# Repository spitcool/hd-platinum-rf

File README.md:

<!-- SPDX-FileCopyrightText: 2026 Christopher Spitler -->
<!-- SPDX-License-Identifier: CC-BY-SA-4.0 OR AGPL-3.0-or-later -->

# hd-platinum-rf

An open-source replacement bridge for Hunter Douglas Platinum blinds and shades,
built around ESP32, with protocol documentation and tools for ongoing research.

## The problem

Hunter Douglas Platinum shades rely on discontinued bridges and remotes. When
that control hardware fails, otherwise working shades become harder to use and
integrate with home automation. The legacy LAN and RF protocols need to be
understood and documented so that replacement controllers can keep them useful.

## The solution

We're building an ESP32-S3 gateway that provides local shade control through a
touchscreen, web interface, and the legacy Platinum network protocol. The current
hardware design uses an M5Stack CoreS3 SE, an Ethernet base, and a custom radio
carrier. Python research tools and a bridge emulator help us capture, understand,
and validate the protocols as the device takes shape.

This project targets the **Platinum generation** of products. It is independent
and unofficial, and does not target the later PowerView system.

## Project status

**We're currently confirming the RF protocols and designing the hardware
implementation.** The project is experimental; the ESP32 gateway is not yet a
validated replacement for the original bridge.

- [x] Document observed LAN commands and initial RF packet formats.
- [x] Build research tools and a bridge emulator with limited observed shade-control results.
- [x] Implement an ESP32-S3 firmware prototype with local controls.
- [ ] Confirm all RF protocols, command timing, and product-specific behavior.
- [ ] Complete and qualify the ESP32 hardware design.
- [ ] Validate enrollment, repeatability, and broader shade compatibility.
- [ ] Validate integrations such as Control4.

See the [RF validation plan](docs/rf-validation-plan.md) for the evidence and
remaining work. Successful software builds and simulations do not establish
physical RF compatibility.

## Getting started

- **Build your own device:** [ESP32 build, flashing, and device BOM](docs/esp32-build.md).
- **Explore the implementation:** [Project details and research tools](docs/project-details.md), including CLI setup and bridge emulator commands.
- **Understand the protocols:** [LAN protocol](docs/lan-protocol.md) and [RF protocol](docs/rf-protocol.md).
- **Review the hardware:** [Carrier design and assembly](hardware/README.md).
- **Run tests or help with RF validation:** [Testing guide](docs/testing.md) and [bench equipment BOM](docs/bom.md).

## Contributing

Protocol validation, hardware review, firmware testing, and documentation
contributions are welcome. Read [CONTRIBUTING.md](CONTRIBUTING.md) for the
workflow, test requirements, and DCO sign-off. Remove private installation data
from shared captures and reports. Use the
[issue tracker](https://github.com/spitcool/hd-platinum-rf/issues) for bugs and
feature discussions.

## License

Host software is [AGPL-3.0-or-later](LICENSE); project firmware is
[GPL-2.0-or-later](LICENSES/GPL-2.0-or-later.txt). Documentation is available under
[CC BY-SA 4.0](LICENSES/CC-BY-SA-4.0.txt) or AGPL-3.0-or-later. See
[LICENSING.md](LICENSING.md) for component boundaries and
[CREDITS.md](CREDITS.md) for third-party attribution.

Hunter Douglas and its product names are trademarks of their respective owner.

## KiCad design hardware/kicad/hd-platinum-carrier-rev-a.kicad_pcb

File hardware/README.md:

<!--
SPDX-FileCopyrightText: 2026 Christopher Spitler
SPDX-License-Identifier: CC-BY-SA-4.0 OR AGPL-3.0-or-later
-->

# Platinum M5Stack radio carrier

This hardware adds an enclosed 2.4 GHz radio to an M5Stack CoreS3 SE and Base
LAN v1.2 stack. The intended product is an Ethernet-connected Platinum shade
bridge with a local TCP service and a small web interface. The radio PCB is designed for
a Module13.2 frame; a coax cable connects it to an external antenna.

**Revision A is an engineering first article.** The CAD and manufacturing
outputs describe a board to build and qualify. They do not establish measured
enclosure fit, RF performance, or compatibility with every Platinum shade.
Complete the [acceptance procedure](manufacturing/acceptance-test.md) before
releasing a repeat build for other users.

The recorded KiCad checks pass with **zero ERC errors/warnings, zero PCB DRC
violations, zero unconnected items and zero schematic-parity differences**;
there are no DRC exclusions. Independent checks passed 95 mechanical/orientation
assertions and 41 manufacturing-package checks and matched 65 connected schematic pins on 17 intended nets.
These check the design files. Physical fit, RF measurements, native-radio
interoperability and the ESP32 firmware remain qualification work. See the
[design-package review](design/final-review.md) for the evidence and limits.

## Appliance architecture

The [final assembly drawing](manufacturing/final-assembly.pdf) shows the
exploded stack, assembled enclosure and a cutaway of the M032 radio layer.
See the [illustrated assembly guide](manufacturing/final-assembly.md) for the
part list and sequence, or open the [SVG](manufacturing/final-assembly.svg).

```text
M5Stack CoreS3 SE K128-SE
  ESP32-S3: application, touchscreen, TCP and HTTP services
                  │ M-Bus power and GPIO
M032 Module13.2 frame + this replacement carrier PCB
  5 V → separate 3.3 V regulator → NiceRF RF2401F20
  dedicated SPI and control GPIO → 2.4 GHz radio
  RF connector → internal coax → external antenna
                  │ all 30 M-Bus contacts pass through
M5Stack Base LAN v1.2 K012-B-V12
  W5500 wired Ethernet and appliance base
```

The custom PCB replaces the M032 prototyping PCB. It is not an adapter soldered
onto the M032 hole grid. The Base LAN and CoreS3 SE remain purchased products.
This carrier does not add Ethernet, PoE, a charger, or another processor.

The radio has a separate SPI bus from the W5500. It uses GPIO 6/5/8 for
SCK/MOSI/MISO and GPIO 18/17/10 for CSN/CE/IRQ. The carrier derives its radio
supply from M-Bus 5 V; its RF 3.3 V rail must not connect to the M5Stack's 3.3 V
rail. The [electrical evidence](design/electrical-evidence.md) and
[pin assignment](design/pin-assignment.csv) record the interface details.

## Files and reproducible build

The complete [hardware review archive](hd-platinum-carrier-rev-a-review.zip)
contains the native source, manufacturing outputs, evidence, tools and license
notices. The archive is for engineering review and first-article planning.
The [tool instructions](tools/README.md) explain how to validate the native CAD
or regenerate it from source. A complete source regeneration and export passed
on the recorded KiCad 9.0.8 toolchain.

## What to send to a manufacturer

Open [the editable KiCad PCB](kicad/hd-platinum-carrier-rev-a.kicad_pcb) and
[schematic](kicad/hd-platinum-carrier-rev-a.kicad_sch), or review the exported
[schematic PDF](manufacturing/schematic.pdf) and
[bottom assembly drawing](manufacturing/assembly-bottom.pdf). The PCB is
50 × 50 mm with all surface-mount parts on the inward-facing bottom side.

Send the [Gerber/drill ZIP](manufacturing/hd-platinum-carrier-rev-a-gerbers.zip),
[PCBA BOM](manufacturing/bom.csv), [placement file](manufacturing/positions.csv),
the [fabrication drawing](manufacturing/fabrication-drawing.pdf),
assembly drawings and these documents together. The [board-only STEP](manufacturing/carrier-board-only.step)
and [outline DXF](manufacturing/board-outline.dxf) support enclosure review;
the STEP does not include components or an enclosure. Keep every file in a handoff
at the same board revision. The editable project and generation tools remain
the source for future revisions.

| Document | Purpose |
| --- | --- |
| [Final assembly drawing and guide](manufacturing/final-assembly.md) | M5Stack stack order, carrier location inside M032, antenna and cable arrangement |
| [Fabrication specification](manufacturing/fabrication.md) | Board construction, RF geometry, drill and DFM requirements |
| [Assembly instructions](manufacturing/assembly.md) | Component handling, orientation, stack assembly and coax installation |
| [Supplier checklist](manufacturing/order-checklist.md) | Quote scope, sourcing, deliverables and release gates |
| [Acceptance procedure](manufacturing/acceptance-test.md) | Bare PCB, assembled carrier and complete appliance tests |
| [Unit traveler template](manufacturing/traveler-template.md) | Per-unit part, measurement and acceptance record |
| [Mechanical evidence](design/mechanical-evidence.md) | Source dimensions, connector and enclosure fit assumptions |
| [Electrical evidence](design/electrical-evidence.md) | Source pinouts, radio constraints and power design |
| [Firmware contract](design/firmware-contract.md) | Initialization, bus ownership, packet-engine limits and porting requirements |
| [Design-package review](design/final-review.md) | Recorded CAD checks, manufacturing cross-check and open physical qualification |

## Purchased system parts

The PCBA BOM covers parts fitted to the custom carrier. These are separate
appliance items; do not accidentally order them once per carrier component.
The machine-readable list is [system-bom.csv](manufacturing/system-bom.csv).

| Item | Manufacturer part / SKU | Quantity per appliance | Procurement note |
| --- | --- | ---: | --- |
| Controller | M5Stack **K128-SE**, CoreS3 SE | 1 | This design's M-Bus assignments target CoreS3 SE. Do not substitute a Core Basic or Core2. |
| Ethernet base | M5Stack **K012-B-V12**, Base LAN v1.2 | 1 | Use v1.2 and verify its switch configuration against the electrical notes. |
| Radio-layer enclosure | M5Stack **M032**, Module13.2 Proto | 1 | Retain the frame; replace the perfboard with this carrier. |
| Assembled carrier | This project, matching board revision | 1 | Includes the exact RF2401F20 module, regulator and RF connector listed in the PCBA BOM. |
| Internal coax pigtail | Taoglas **CAB.628** | 1 | 95 mm, 1.13 mm coax; I-PEX MHF I board plug to RP-SMA female bulkhead. Verify cable routing and enclosure wall fit. |
| External antenna | Taoglas **GW.11.A153** | 1 | 2.4 GHz hinged antenna, RP-SMA male; matches CAB.628. Actual installation/range requires qualification. |
| Stack fasteners | Sized to the measured final assembly | 1 set | CoreS3 stacks can need different lengths at different positions. Do not select from total case height alone. |
| Power supply with captive USB-C cable | Raspberry Pi **SC0218**, black US 15 W supply | 1 | Fixed 5.1 V / 3 A into CoreS3 SE USB-C; enable M-Bus 5 V in firmware. Leave the LAN base's separate DC input unconnected. Qualify whole-stack startup/current. |

Manufacturer product references: [CoreS3 SE](https://docs.m5stack.com/en/core/CoreS3-SE),
[Base LAN v1.2](https://docs.m5stack.com/en/base/Base_LAN_v1.2),
[Module13.2 Proto](https://shop.m5stack.com/products/proto-module-13-2).
The selected RF accessory specifications are
[CAB.628](https://www.taoglas.com/datasheets/CAB.628.pdf) and
[GW.11.A153](https://cdn.taoglas.com/datasheets/GW.11.A153.pdf).
The power supply SKU and output rating are documented in the
[Raspberry Pi product brief](https://datasheets.raspberrypi.org/power-supply/usb-c-power-supply-product-brief.pdf).

## Firmware boundary

This board does not execute the repository's Python service unchanged. It
needs ESP32-S3 firmware implementing the radio driver and the appliance
services. Current host software provides a behavioral reference; its observed
TCP port is 522 and its HTTP service defaults to port 8077.

The RF2401F20 is selected for its nRF24L01+ radio architecture, including the
250 kbps mode relevant to the working bladeRF path. SDR success does not itself
prove that this carrier's hardware packet engine will produce the required
packet-control fields, sequence behavior and burst timing. Capture and compare
the first article's actual transmission before claiming shade interoperability.
See the existing [RF protocol findings](../docs/rf-protocol.md) and
[bridge behavior](../docs/bridge-prototype.md).

Before distribution, freeze a tested firmware version with the PCBA and
system BOM. A populated board without that firmware is not a completed shade
bridge. New firmware belongs in its own component under the repository's
[firmware licensing policy](../LICENSING.md#firmware).

## Source and licensing

The [hardware licensing and attribution record](LICENSE.md) identifies the
original design and redistributed KiCad library scopes. Project-authored documentation in this directory follows the repository's
`CC-BY-SA-4.0 OR AGPL-3.0-or-later` documentation policy. CAD/generator licensing
is recorded in the relevant source files. Vendor reference documents remain
the vendors' material; citations and factual measurements do not transfer
their licenses. Do not include downloaded vendor PDFs in an outgoing source
package unless their redistribution terms permit it.

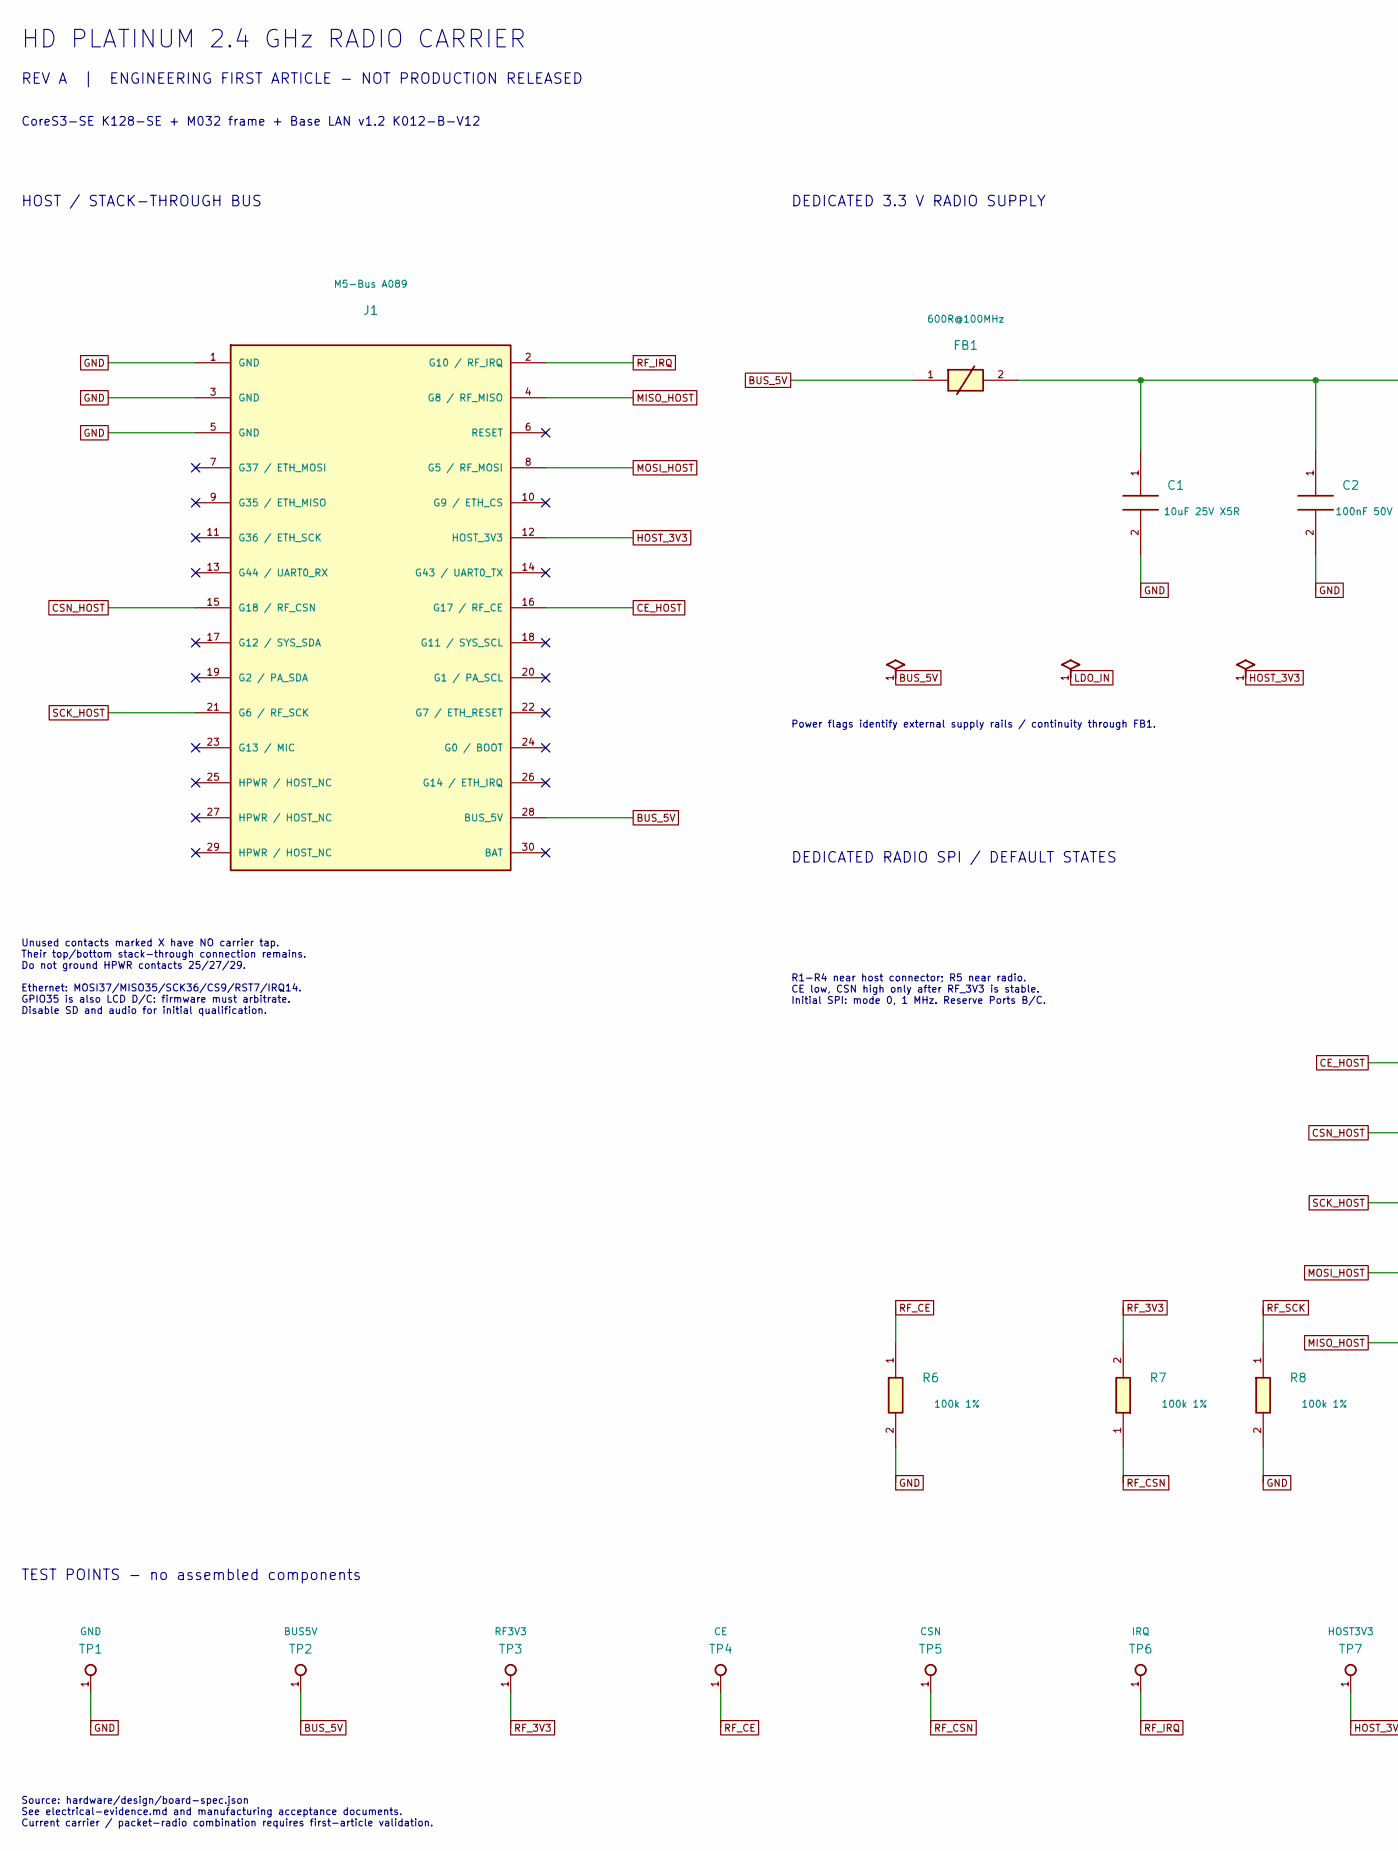
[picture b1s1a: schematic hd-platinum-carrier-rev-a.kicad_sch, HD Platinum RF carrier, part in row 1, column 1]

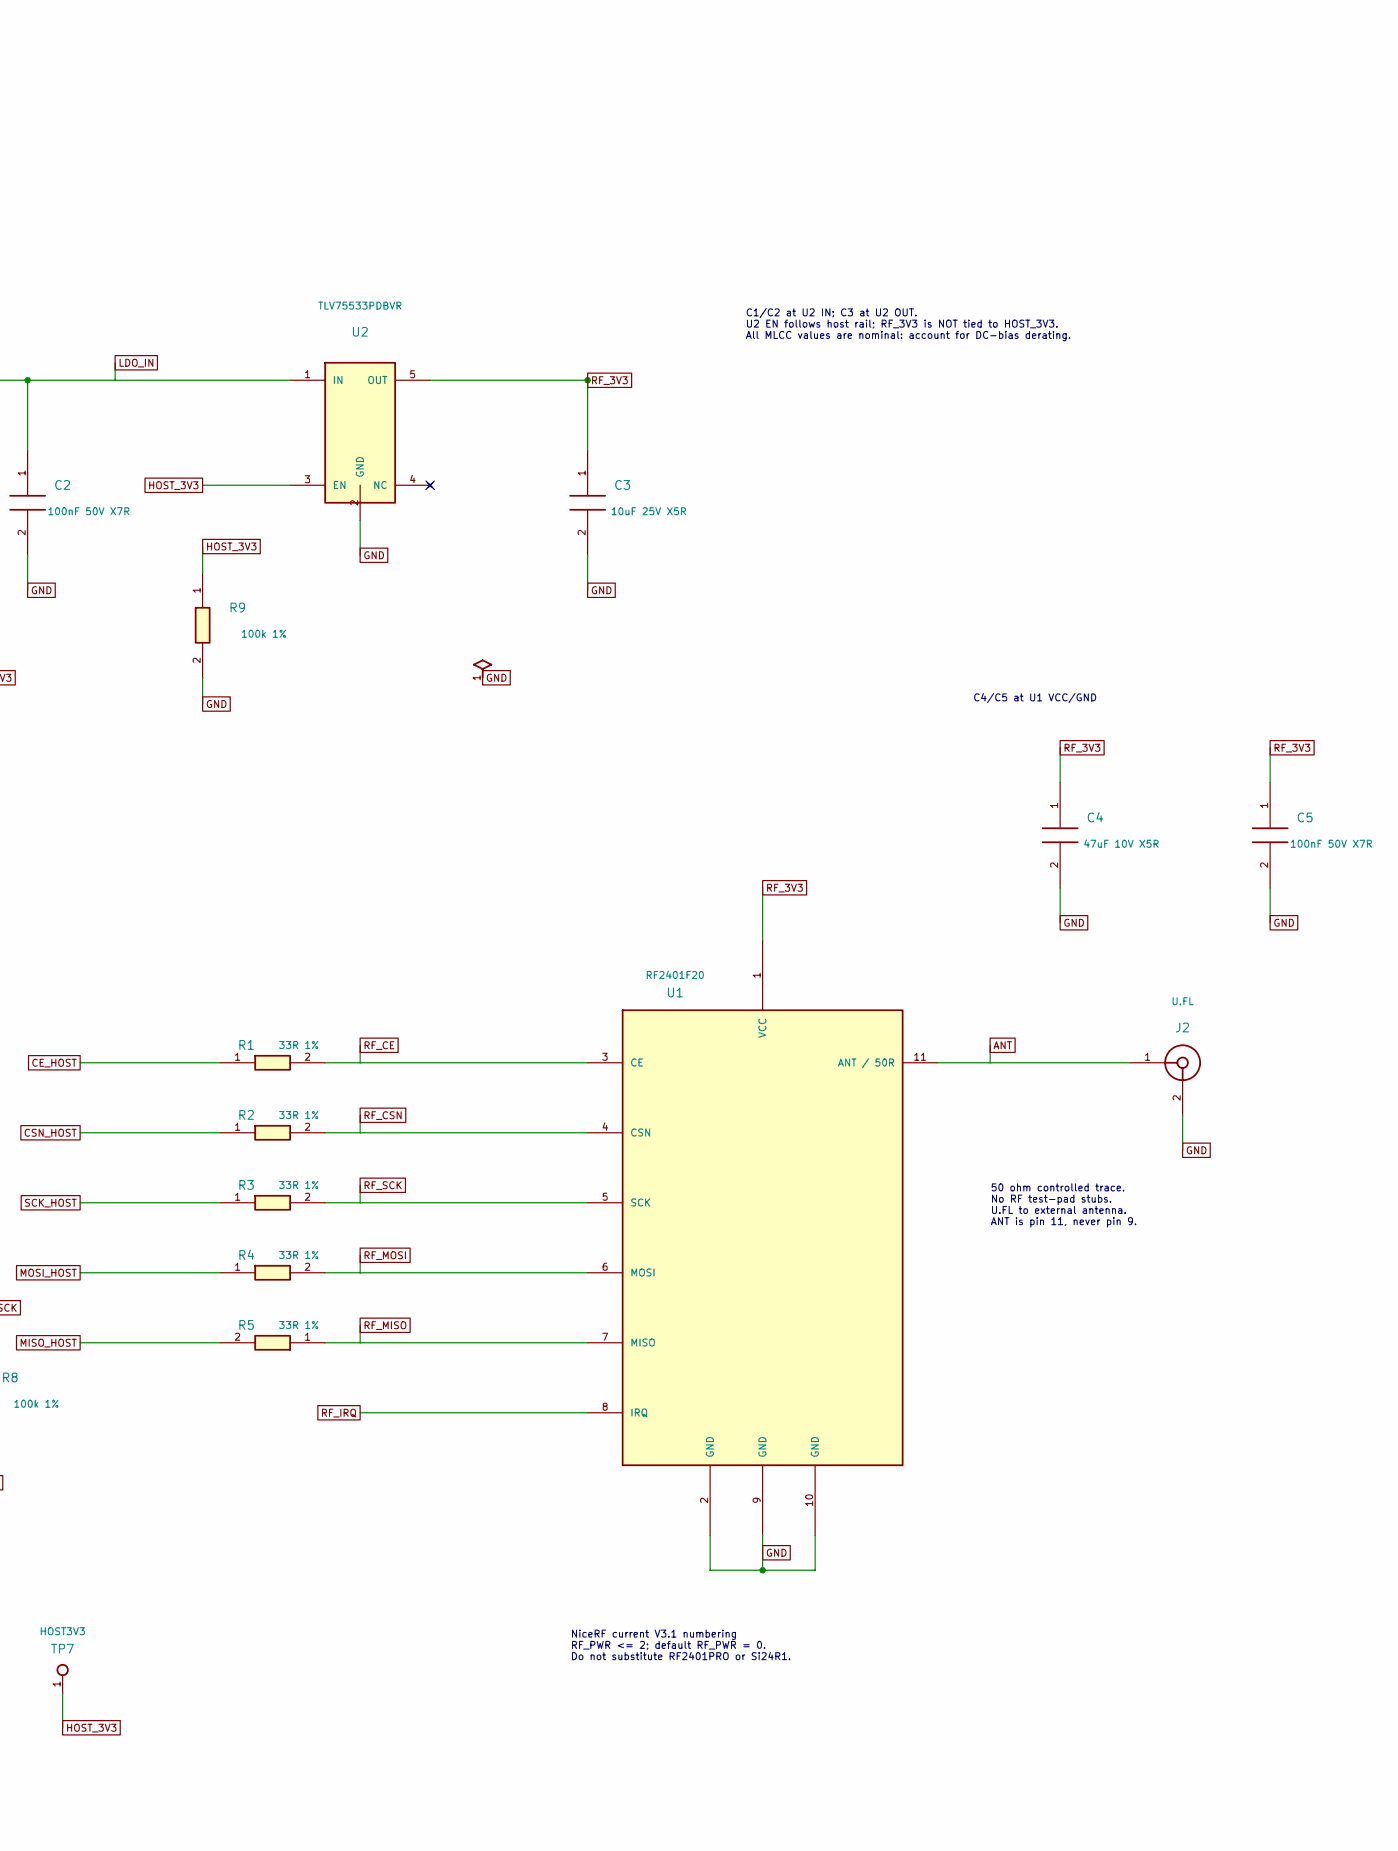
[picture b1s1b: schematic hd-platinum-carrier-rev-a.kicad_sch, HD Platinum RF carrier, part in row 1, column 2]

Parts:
C1, C3: 10uF 25V X5R; C_0805_2012Metric; MPN CL21A106KAYNNNE
C2, C5: 100nF 50V X7R; C_0603_1608Metric; MPN CL10B104KB8NNNC
C4: 47uF 10V X5R; C_1206_3216Metric; MPN CL31A476MPHNNNE
FB1: 600R@100MHz; L_0603_1608Metric; MPN BLM18AG601SN1D
J1: M5-Bus A089; M5Bus_A089_2x15; MPN A089
J2: U.FL; U.FL_Hirose_U.FL-R-SMT-1_Vertical; MPN U.FL-R-SMT-1(10)
R1, R2, R3, R4, R5: 33R 1%; R_0603_1608Metric; MPN RC0603FR-0733RL
R6, R7, R8, R9: 100k 1%; R_0603_1608Metric; MPN RC0603FR-07100KL
TP1: GND; TestPoint_Pad_D1.0mm; MPN PCB feature
TP2: BUS5V; TestPoint_Pad_D1.0mm; MPN PCB feature
TP3: RF3V3; TestPoint_Pad_D1.0mm; MPN PCB feature
TP4: CE; TestPoint_Pad_D1.0mm; MPN PCB feature
TP5: CSN; TestPoint_Pad_D1.0mm; MPN PCB feature
TP6: IRQ; TestPoint_Pad_D1.0mm; MPN PCB feature
TP7: HOST3V3; TestPoint_Pad_D1.0mm; MPN PCB feature
U1: RF2401F20; NiceRF_RF2401F20; MPN RF2401F20
U2: TLV75533PDBVR; SOT-23-5; MPN TLV75533PDBVR

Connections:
ANT: J2.1 (ANT), U1.11 (ANT / 50R)
BUS_5V: FB1.1, J1.28 (BUS_5V), TP2.1
CE_HOST: J1.16 (G17 / RF_CE), R1.1
CSN_HOST: J1.15 (G18 / RF_CSN), R2.1
GND: C1.2, C2.2, C3.2, C4.2, C5.2, J1.1 (GND), J1.3 (GND), J1.5 (GND), J2.2 (GND), R6.2, R8.2, R9.2, TP1.1, U1.2 (GND), U1.9 (GND), U1.10 (GND), U2.2 (GND)
HOST_3V3: J1.12 (HOST_3V3), R9.1, TP7.1, U2.3 (EN)
LDO_IN: C1.1, C2.1, FB1.2, U2.1 (IN)
MISO_HOST: J1.4 (G8 / RF_MISO), R5.2
MOSI_HOST: J1.8 (G5 / RF_MOSI), R4.1
RF_3V3: C3.1, C4.1, C5.1, R7.2, TP3.1, U1.1 (VCC), U2.5 (OUT)
RF_CE: R1.2, R6.1, TP4.1, U1.3 (CE)
RF_CSN: R2.2, R7.1, TP5.1, U1.4 (CSN)
RF_IRQ: J1.2 (G10 / RF_IRQ), TP6.1, U1.8 (IRQ)
RF_MISO: R5.1, U1.7 (MISO)
RF_MOSI: R4.2, U1.6 (MOSI)
RF_SCK: R3.2, R8.1, U1.5 (SCK)
SCK_HOST: J1.21 (G6 / RF_SCK), R3.1

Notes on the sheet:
HD PLATINUM 2.4 GHz RADIO CARRIER
REV A | ENGINEERING FIRST ARTICLE - NOT PRODUCTION RELEASED
CoreS3-SE K128-SE + M032 frame + Base LAN v1.2 K012-B-V12
HOST / STACK-THROUGH BUS
DEDICATED 3.3 V RADIO SUPPLY
C1/C2 at U2 IN; C3 at U2 OUT. U2 EN follows host rail; RF_3V3 is NOT tied to HOST_3V3. All MLCC values are nominal: account for DC-bias derating.
Power flags identify external supply rails / continuity through FB1.
DEDICATED RADIO SPI / DEFAULT STATES
C4/C5 at U1 VCC/GND
50 ohm controlled trace. No RF test-pad stubs. U.FL to external antenna. ANT is pin 11, never pin 9.
NiceRF current V3.1 numbering RF_PWR <= 2; default RF_PWR = 0. Do not substitute RF2401PRO or Si24R1.
R1-R4 near host connector; R5 near radio. CE low, CSN high only after RF_3V3 is stable. Initial SPI: mode 0, 1 MHz. Reserve Ports B/C.
Unused contacts marked X have NO carrier tap. Their top/bottom stack-through connection remains. Do not ground HPWR contacts 25/27/29. Ethernet: MOSI37/MISO35/SCK36/CS9/RST7/IRQ14. GPIO35 is also LCD D/C: firmware must arbitrate. Disable SD and audio for initial qualification.
TEST POINTS - no assembled components
Source: hardware/design/board-spec.json See electrical-evidence.md and manufacturing acceptance documents. Current carrier / packet-radio combination requires first-article validation.

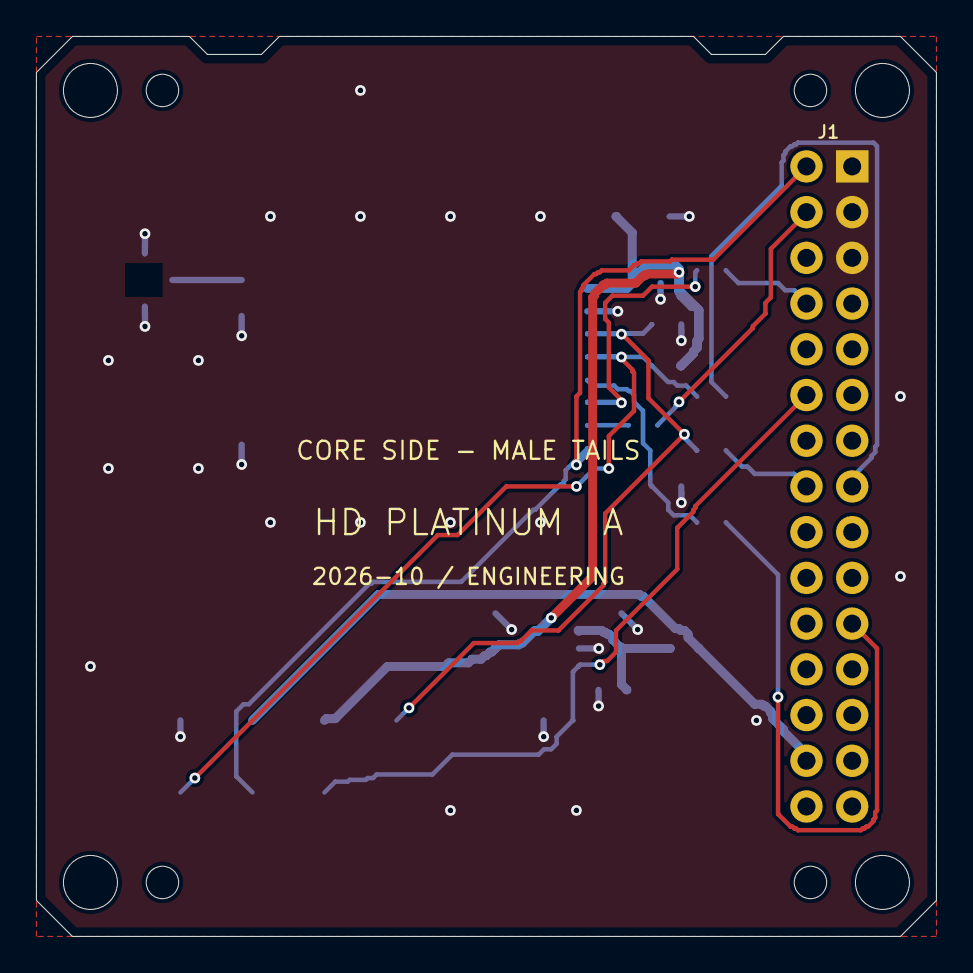
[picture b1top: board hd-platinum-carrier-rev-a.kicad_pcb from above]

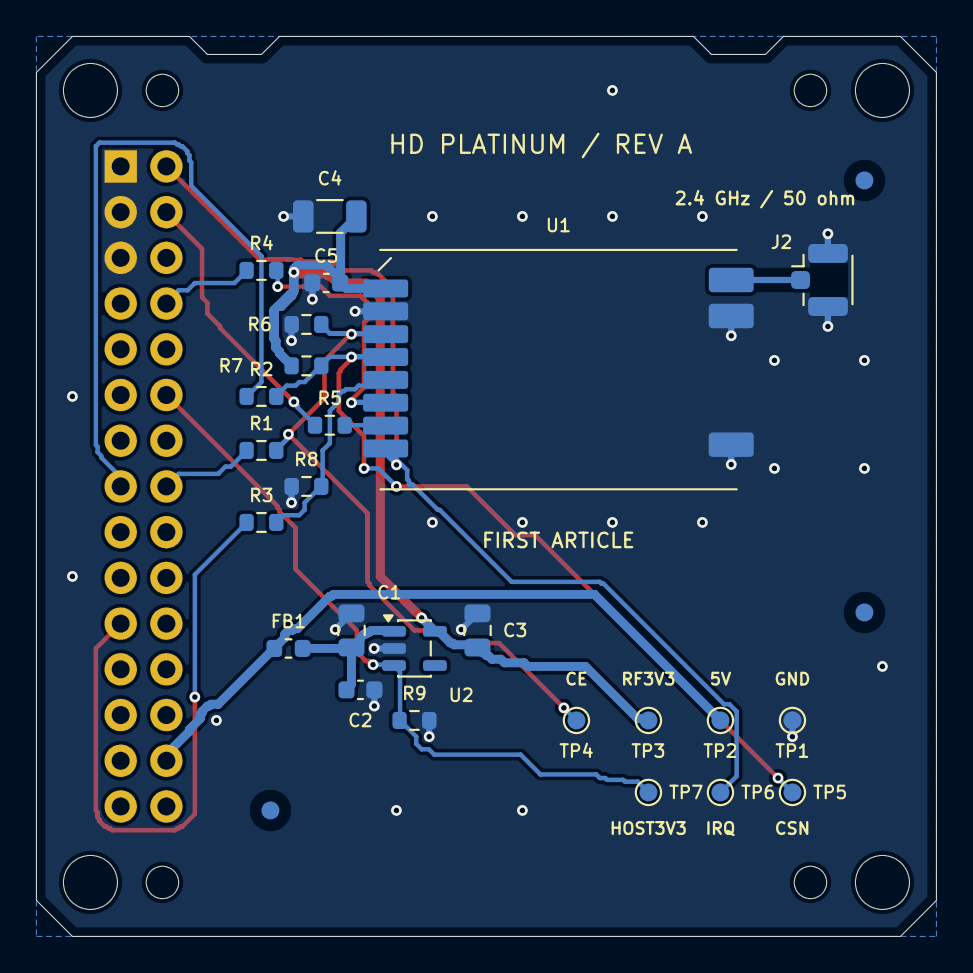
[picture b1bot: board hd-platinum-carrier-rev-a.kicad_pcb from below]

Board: 4 copper layers, 50.0 x 50.0 mm, 37 parts (29 on the bottom side), 17 nets.

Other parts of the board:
FID1, FID2, FID3: 1mm fiducial; Fiducial_1mm
H1, H2, H3, H4: 3mm NPTH; MountingHole_3mm
H5, H6, H7, H8: 1.8mm NPTH; MountingHole_1.8mm

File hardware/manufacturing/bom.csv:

Designator,Quantity,Value,Manufacturer,MPN,Footprint,Side,Supplier reference,Assembly,Notes
J1,1,M5-Bus A089,M5Stack,A089,HDPlatinum:M5Bus_A089_2x15,Bottom,,Manual through-hole,Housing on bottom; male tails toward CoreS3 SE. 1 piece from A089 10-pack.
U1,1,RF2401F20,NiceRF,RF2401F20,HDPlatinum:NiceRF_RF2401F20,Bottom,LCSC C5126685,SMT,No RF2401PRO/Si24R1 substitutions. Shield outward. RF_PWR <=2; start at0.
J2,1,U.FL,Hirose,U.FL-R-SMT-1(10),Connector_Coaxial:U.FL_Hirose_U.FL-R-SMT-1_Vertical,Bottom,,SMT,
U2,1,TLV75533PDBVR,Texas Instruments,TLV75533PDBVR,Package_TO_SOT_SMD:SOT-23-5,Bottom,,SMT,
FB1,1,600R@100MHz,Murata,BLM18AG601SN1D,Inductor_SMD:L_0603_1608Metric,Bottom,,SMT,
C1,1,10uF 25V X5R,Samsung,CL21A106KAYNNNE,Capacitor_SMD:C_0805_2012Metric,Bottom,LCSC C15850,SMT,
C2,1,100nF 50V X7R,Samsung,CL10B104KB8NNNC,Capacitor_SMD:C_0603_1608Metric,Bottom,LCSC C1591,SMT,
C3,1,10uF 25V X5R,Samsung,CL21A106KAYNNNE,Capacitor_SMD:C_0805_2012Metric,Bottom,LCSC C15850,SMT,
C4,1,47uF 10V X5R,Samsung,CL31A476MPHNNNE,Capacitor_SMD:C_1206_3216Metric,Bottom,LCSC C96123,SMT,
C5,1,100nF 50V X7R,Samsung,CL10B104KB8NNNC,Capacitor_SMD:C_0603_1608Metric,Bottom,LCSC C1591,SMT,
R1,1,33R 1%,Yageo,RC0603FR-0733RL,Resistor_SMD:R_0603_1608Metric,Bottom,,SMT,
R2,1,33R 1%,Yageo,RC0603FR-0733RL,Resistor_SMD:R_0603_1608Metric,Bottom,,SMT,
R3,1,33R 1%,Yageo,RC0603FR-0733RL,Resistor_SMD:R_0603_1608Metric,Bottom,,SMT,
R4,1,33R 1%,Yageo,RC0603FR-0733RL,Resistor_SMD:R_0603_1608Metric,Bottom,,SMT,
R5,1,33R 1%,Yageo,RC0603FR-0733RL,Resistor_SMD:R_0603_1608Metric,Bottom,,SMT,
R6,1,100k 1%,Yageo,RC0603FR-07100KL,Resistor_SMD:R_0603_1608Metric,Bottom,,SMT,
R7,1,100k 1%,Yageo,RC0603FR-07100KL,Resistor_SMD:R_0603_1608Metric,Bottom,,SMT,
R8,1,100k 1%,Yageo,RC0603FR-07100KL,Resistor_SMD:R_0603_1608Metric,Bottom,,SMT,
R9,1,100k 1%,Yageo,RC0603FR-07100KL,Resistor_SMD:R_0603_1608Metric,Bottom,,SMT,
